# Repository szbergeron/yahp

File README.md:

WARN: Not ready for use yet

The boards are semi-final, but I need to finish part selection and push a new variant that allows varying sensor position.
Code is in Proof-of-Concept state, and has a lot of stuff hard-coded that should be pulled out into configs.

#Because getting an AvantGrand would just be way too easy

Inspired by [Greg Zweigle's DIY Hybrid Piano](https://github.com/gzweigle/DIY-Grand-Digital-Piano) and the [Cybrid Project](https://github.com/ekumanov/cybrid).

I don't come from a hardware/EE background, so a lot of that stuff was done by feel rather than through meticulous science. Instead, I tried to all of the "magic" through software. The sensors are probably not "ideal", but they are cheap and dumb simple. I didn't use trimmers or anything like that to calibrate, opting instead to gather raw measurements and then apply software correction. I also opted to use onboard ADCs instead of external ones or any kind of extra voltage reference. This absolutely introduces some inaccuracy in the lower bits of the raw measurements, but again--software magic :)

The flip side of using such a simple design from an EE perspective is that fabrication is _dumb simple_, even if technically more expensive when looking at the BOM. Each key uses a single sensor, and there is an MCU for every 16 keys, plus some basic power filtering all on a PCB. I'm spectacularly bad at soldering, so this has as little of it as I could get away with. This project is aimed at being an easy "kit" to get components for and assemble. Follow along if you'd like!

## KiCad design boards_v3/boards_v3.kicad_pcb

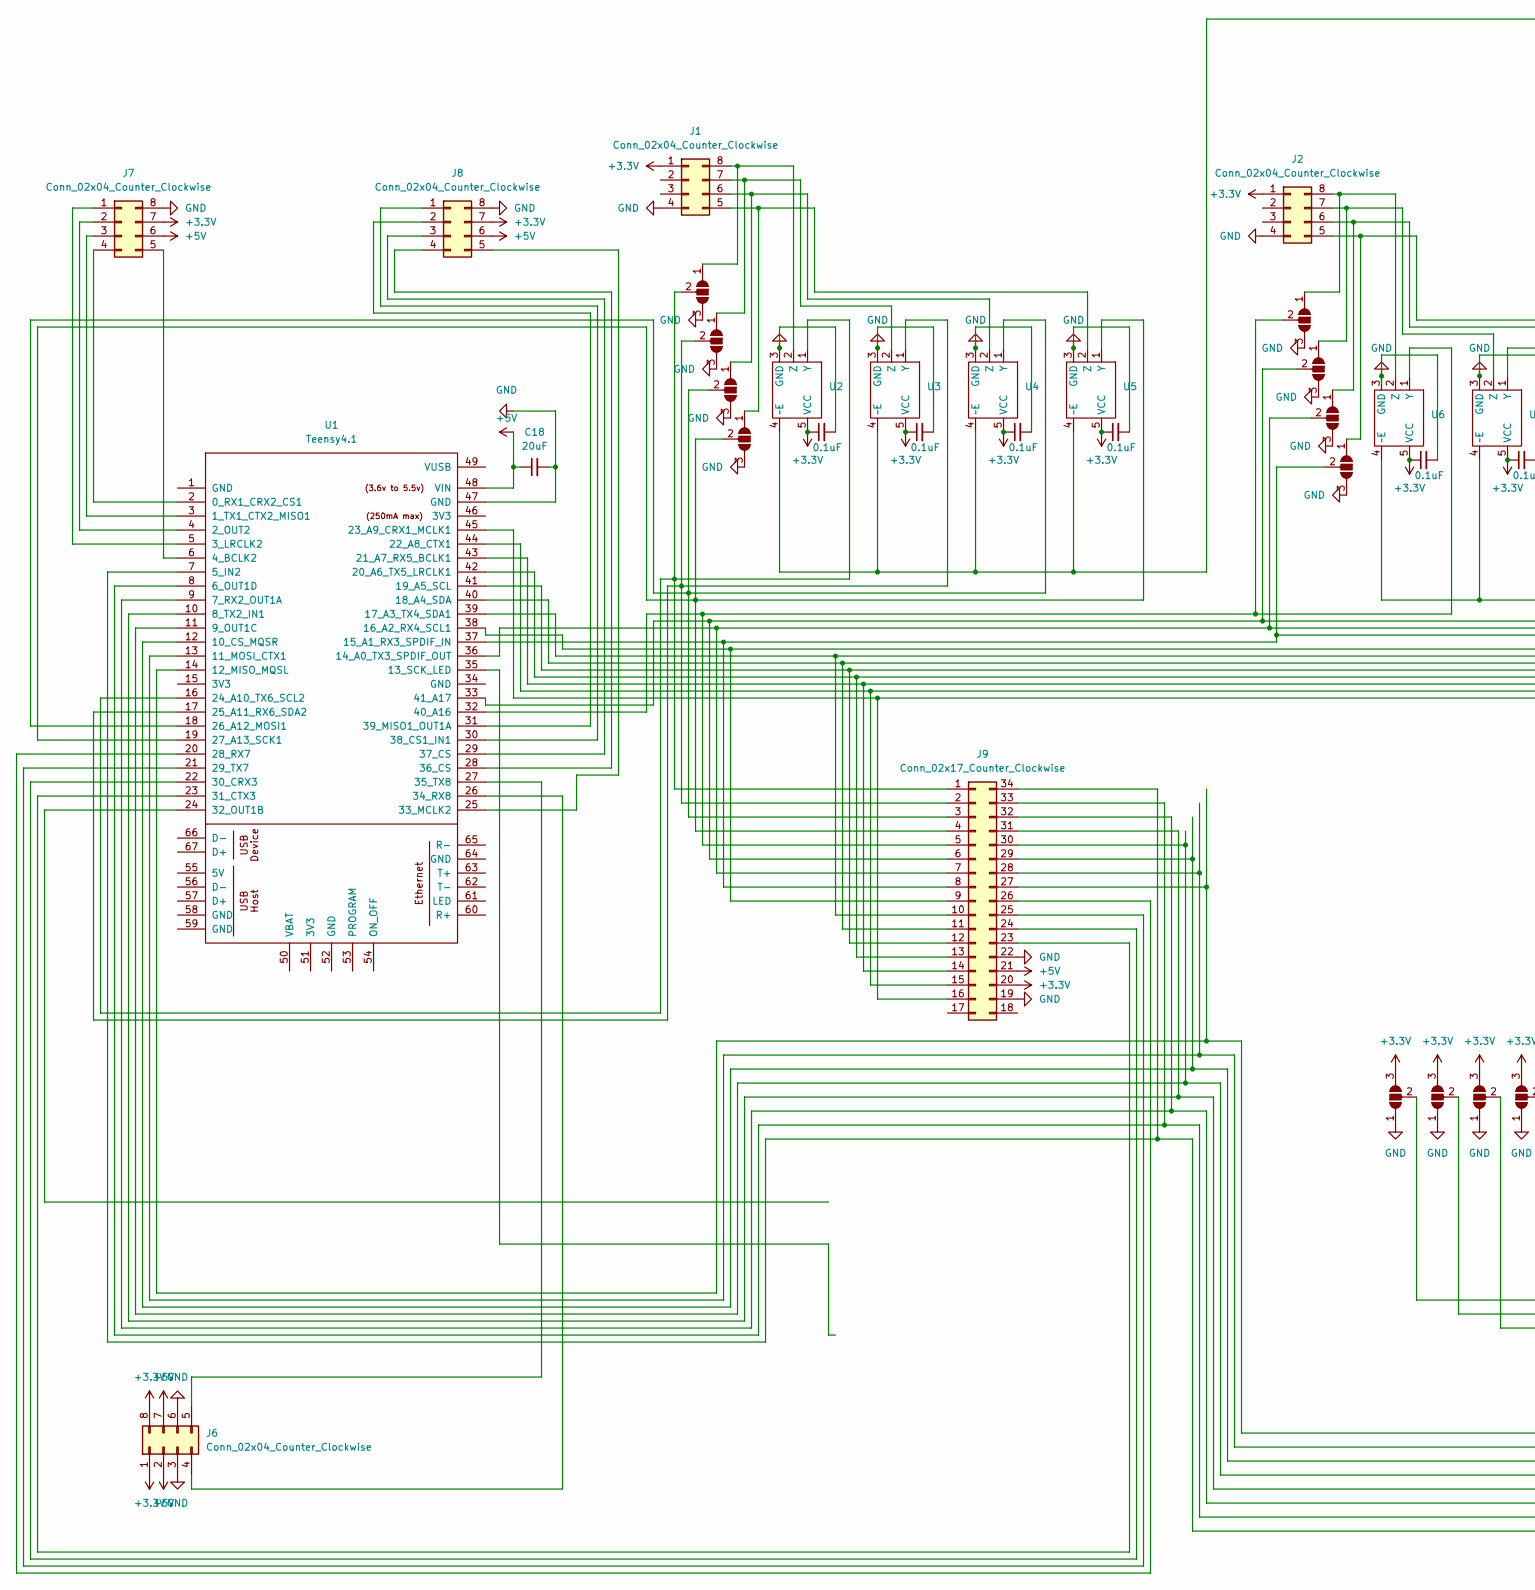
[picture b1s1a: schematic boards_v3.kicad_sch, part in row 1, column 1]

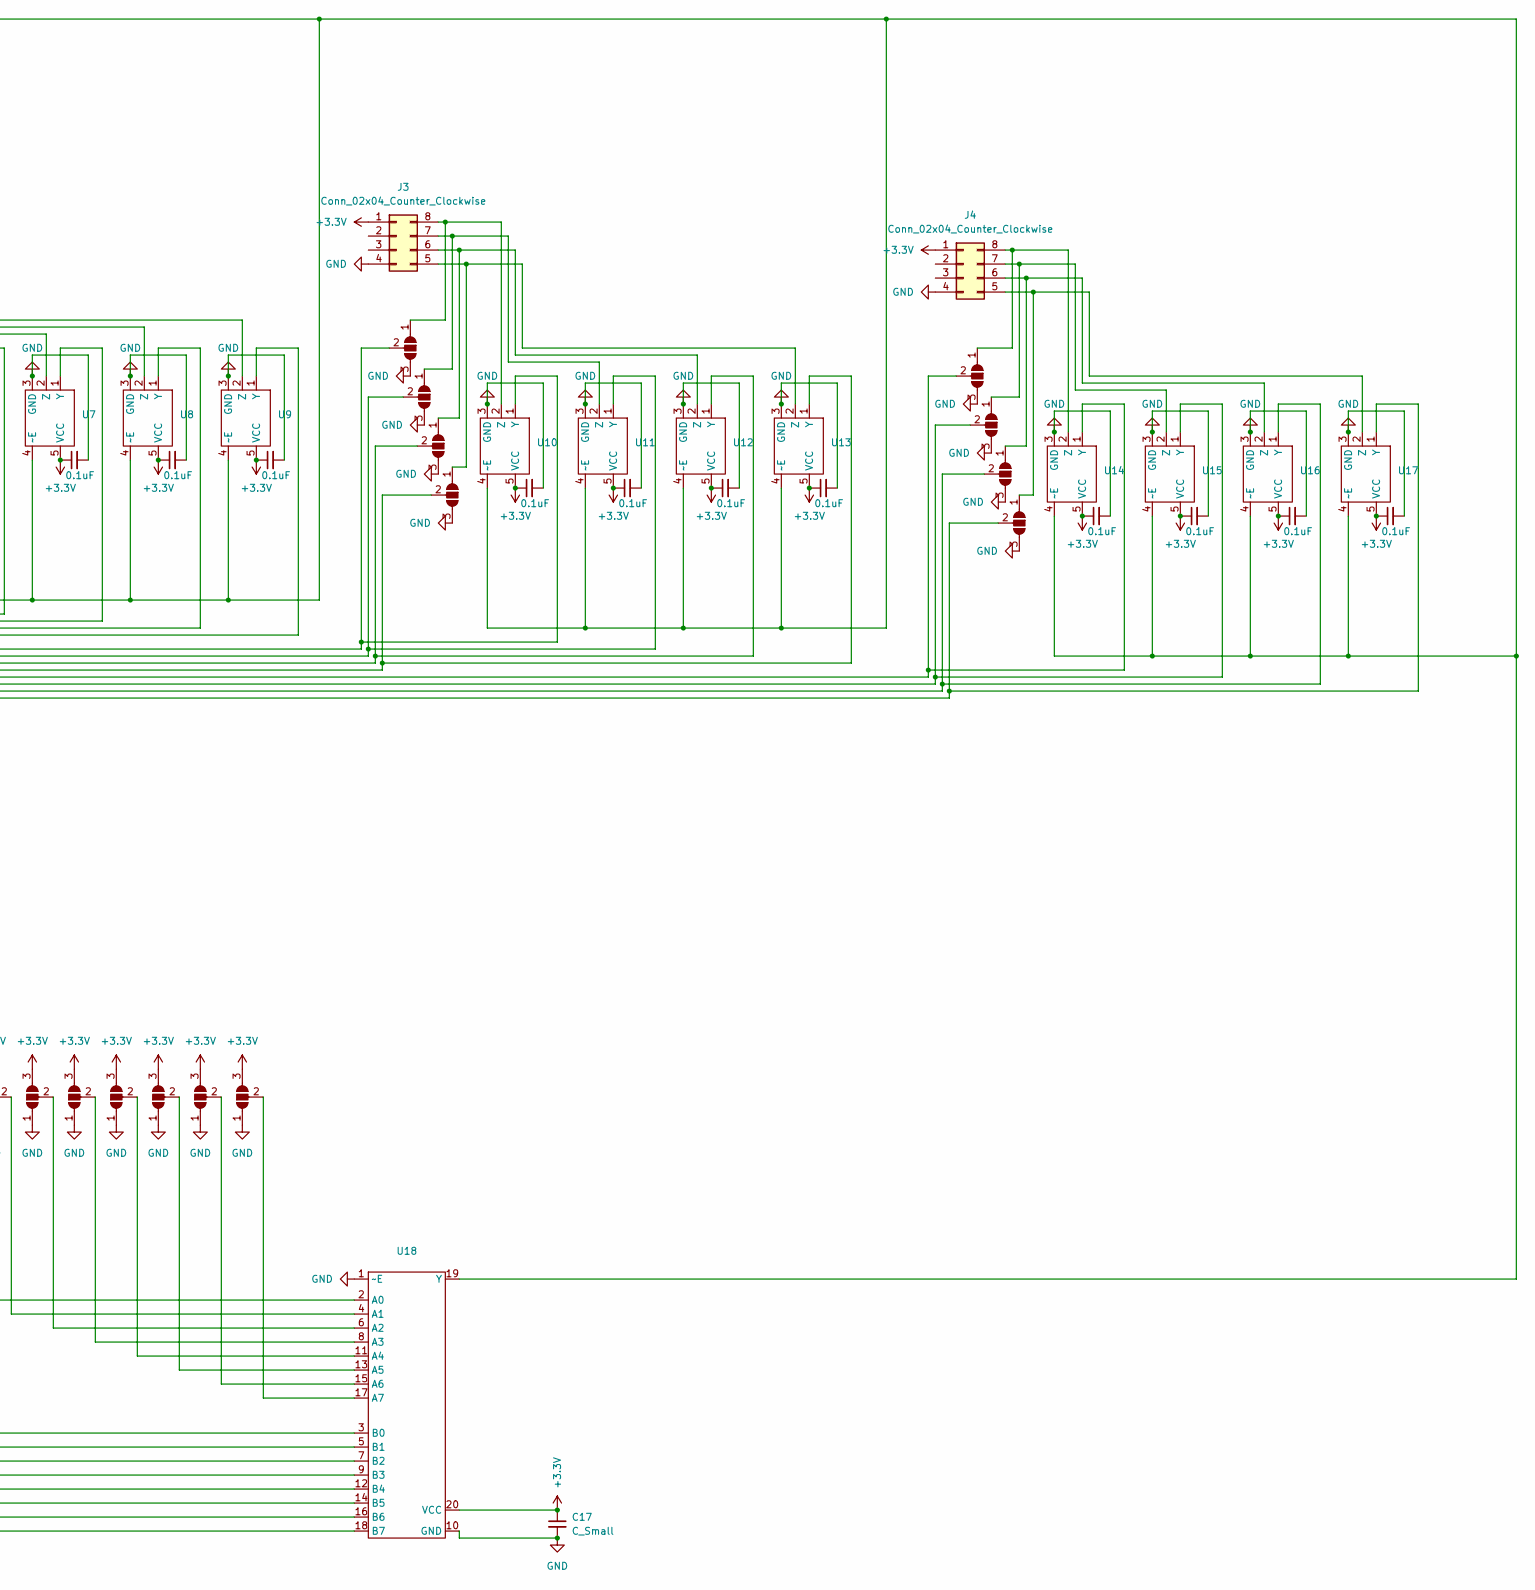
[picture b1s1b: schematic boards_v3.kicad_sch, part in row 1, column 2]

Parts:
C1, C2, C3, C4, C5, C6, C7, C8, C9, C10, C11, C12, C13, C14, C15, C16: 0.1uF; C_1206_3216Metric_Pad1.33x1.80mm_HandSolder
C17: C_Small; C_1206_3216Metric_Pad1.33x1.80mm_HandSolder
C18: 20uF; C_1812_4532Metric_Pad1.57x3.40mm_HandSolder
J1, J2, J3, J4, J6, J7, J8: Conn_02x04_Counter_Clockwise; Conn_02x04_2.54mm_pin
J9: Conn_02x17_Counter_Clockwise; Conn_02x17_2.54mm_pin
JP1, JP2, JP3, JP4, JP5, JP6, JP7, JP8, JP9, JP10, JP11, JP12, JP13, JP14, JP15, JP16, JP17, JP18, JP19, JP20, JP21, JP22, JP23, JP24: SolderJumper_3_Open; SolderJumper-3_P1.3mm_Open_RoundedPad1.0x1.5mm
U1: Teensy4.1; Teensy41
U2, U3, U4, U5, U6, U7, U8, U9, U10, U11, U12, U13, U14, U15, U16, U17: SC-74A-5_1.55x2.9mm_P0.95mm
U18: SOIC-20W_7.5x12.8mm_P1.27mm

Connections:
+3.3V: C1.1, C2.1, C3.1, C4.1, C5.1, C6.1, C7.1, C8.1, C9.1, C10.1, C11.1, C12.1, C13.1, C14.1, C15.1, C16.1, C17.1, J1.1, J2.1, J3.1, J4.1, J6.1, J6.8, J7.7, J8.7, J9.20, JP17.3 (B), JP18.3 (B), JP19.3 (B), JP20.3 (B), JP21.3 (B), JP22.3 (B), JP23.3 (B), JP24.3 (B), U2.5 (VCC), U3.5 (VCC), U4.5 (VCC), U5.5 (VCC), U6.5 (VCC), U7.5 (VCC), U8.5 (VCC), U9.5 (VCC), U10.5 (VCC), U11.5 (VCC), U12.5 (VCC), U13.5 (VCC), U14.5 (VCC), U15.5 (VCC), U16.5 (VCC), U17.5 (VCC), U18.20 (VCC)
+5V: C18.1, J6.2, J6.7, J7.6, J8.6, J9.21, U1.48 (VIN)
GND: C1.2, C2.2, C3.2, C4.2, C5.2, C6.2, C7.2, C8.2, C9.2, C10.2, C11.2, C12.2, C13.2, C14.2, C15.2, C16.2, C17.2, C18.2, J1.4, J2.4, J3.4, J4.4, J6.3, J6.6, J7.8, J8.8, J9.19, J9.22, JP1.3 (B), JP2.3 (B), JP3.3 (B), JP4.3 (B), JP5.3 (B), JP6.3 (B), JP7.3 (B), JP8.3 (B), JP9.3 (B), JP10.3 (B), JP11.3 (B), JP12.3 (B), JP13.3 (B), JP14.3 (B), JP15.3 (B), JP16.3 (B), JP17.1 (A), JP18.1 (A), JP19.1 (A), JP20.1 (A), JP21.1 (A), JP22.1 (A), JP23.1 (A), JP24.1 (A), U1.47 (GND), U2.3 (GND), U3.3 (GND), U4.3 (GND), U5.3 (GND), U6.3 (GND), U7.3 (GND), U8.3 (GND), U9.3 (GND), U10.3 (GND), U11.3 (GND), U12.3 (GND), U13.3 (GND), U14.3 (GND), U15.3 (GND), U16.3 (GND), U17.3 (GND), U18.1 (~E), U18.10 (GND)
unnamed: J1.5, JP4.1 (A), U5.2 (Z)
unnamed: J1.6, JP3.1 (A), U4.2 (Z)
unnamed: J1.7, JP2.1 (A), U3.2 (Z)
unnamed: J1.8, JP1.1 (A), U2.2 (Z)
unnamed: J2.5, JP8.1 (A), U9.2 (Z)
unnamed: J2.6, JP7.1 (A), U8.2 (Z)
unnamed: J2.7, JP6.1 (A), U7.2 (Z)
unnamed: J2.8, JP5.1 (A), U6.2 (Z)
unnamed: J3.5, JP12.1 (A), U13.2 (Z)
unnamed: J3.6, JP11.1 (A), U12.2 (Z)
unnamed: J3.7, JP10.1 (A), U11.2 (Z)
unnamed: J3.8, JP9.1 (A), U10.2 (Z)
unnamed: J4.5, JP16.1 (A), U17.2 (Z)
unnamed: J4.6, JP15.1 (A), U16.2 (Z)
unnamed: J4.7, JP14.1 (A), U15.2 (Z)
unnamed: J4.8, JP13.1 (A), U14.2 (Z)
unnamed: J6.4, U1.26 (34_RX8)
unnamed: J6.5, U1.27 (35_TX8)
unnamed: J7.1, U1.5 (3_LRCLK2)
unnamed: J7.2, U1.4 (2_OUT2)
unnamed: J7.3, U1.3 (1_TX1_CTX2_MISO1)
unnamed: J7.4, U1.2 (0_RX1_CRX2_CS1)
unnamed: J7.5, U1.6 (4_BCLK2)
unnamed: J8.1, U1.30 (38_CS1_IN1)
unnamed: J8.2, U1.31 (39_MISO1_OUT1A)
unnamed: J8.3, U1.29 (37_CS)
unnamed: J8.4, U1.28 (36_CS)
unnamed: J8.5, U1.25 (33_MCLK2)
unnamed: J9.1, JP1.2 (C), U1.16 (24_A10_TX6_SCL2), U2.1 (Y)
unnamed: J9.2, JP2.2 (C), U1.17 (25_A11_RX6_SDA2), U3.1 (Y)
unnamed: J9.3, JP3.2 (C), U1.18 (26_A12_MOSI1), U4.1 (Y)
unnamed: J9.4, JP4.2 (C), U1.19 (27_A13_SCK1), U5.1 (Y)
unnamed: J9.5, JP5.2 (C), U1.32 (40_A16), U6.1 (Y)
unnamed: J9.6, JP6.2 (C), U1.33 (41_A17), U7.1 (Y)
unnamed: J9.7, JP7.2 (C), U1.36 (14_A0_TX3_SPDIF_OUT), U8.1 (Y)
unnamed: J9.8, JP8.2 (C), U1.37 (15_A1_RX3_SPDIF_IN), U9.1 (Y)
unnamed: J9.9, JP9.2 (C), U1.38 (16_A2_RX4_SCL1), U10.1 (Y)
unnamed: J9.10, JP10.2 (C), U1.39 (17_A3_TX4_SDA1), U11.1 (Y)
unnamed: J9.11, JP11.2 (C), U1.40 (18_A4_SDA), U12.1 (Y)
unnamed: J9.12, JP12.2 (C), U1.41 (19_A5_SCL), U13.1 (Y)
unnamed: J9.13, JP13.2 (C), U1.42 (20_A6_TX5_LRCLK1), U14.1 (Y)
unnamed: J9.14, JP14.2 (C), U1.43 (21_A7_RX5_BCLK1), U15.1 (Y)
unnamed: J9.15, JP15.2 (C), U1.44 (22_A8_CTX1), U16.1 (Y)
unnamed: J9.16, JP16.2 (C), U1.45 (23_A9_CRX1_MCLK1), U17.1 (Y)
unnamed: J9.23, U1.23 (31_CTX3)
unnamed: J9.24, U1.22 (30_CRX3)
unnamed: J9.25, U1.21 (29_TX7)
unnamed: J9.26, U1.20 (28_RX7)
unnamed: J9.27, U1.14 (12_MISO_MQSL), U18.3 (B0)
unnamed: J9.28, U1.13 (11_MOSI_CTX1), U18.5 (B1)
unnamed: J9.29, U1.12 (10_CS_MQSR), U18.7 (B2)
unnamed: J9.30, U1.11 (9_OUT1C), U18.9 (B3)
unnamed: J9.31, U1.10 (8_TX2_IN1), U18.12 (B4)
unnamed: J9.32, U1.9 (7_RX2_OUT1A), U18.14 (B5)
unnamed: J9.33, U1.8 (6_OUT1D), U18.16 (B6)
unnamed: J9.34, U1.7 (5_IN2), U18.18 (B7)
unnamed: JP17.2 (C), U18.2 (A0)
unnamed: JP18.2 (C), U18.4 (A1)
unnamed: JP19.2 (C), U18.6 (A2)
unnamed: JP20.2 (C), U18.8 (A3)
unnamed: JP21.2 (C), U18.11 (A4)
unnamed: JP22.2 (C), U18.13 (A5)
unnamed: JP23.2 (C), U18.15 (A6)
unnamed: JP24.2 (C), U18.17 (A7)
unnamed: U2.4 (~E), U3.4 (~E), U4.4 (~E), U5.4 (~E), U6.4 (~E), U7.4 (~E), U8.4 (~E), U9.4 (~E), U10.4 (~E), U11.4 (~E), U12.4 (~E), U13.4 (~E), U14.4 (~E), U15.4 (~E), U16.4 (~E), U17.4 (~E), U18.19 (Y)

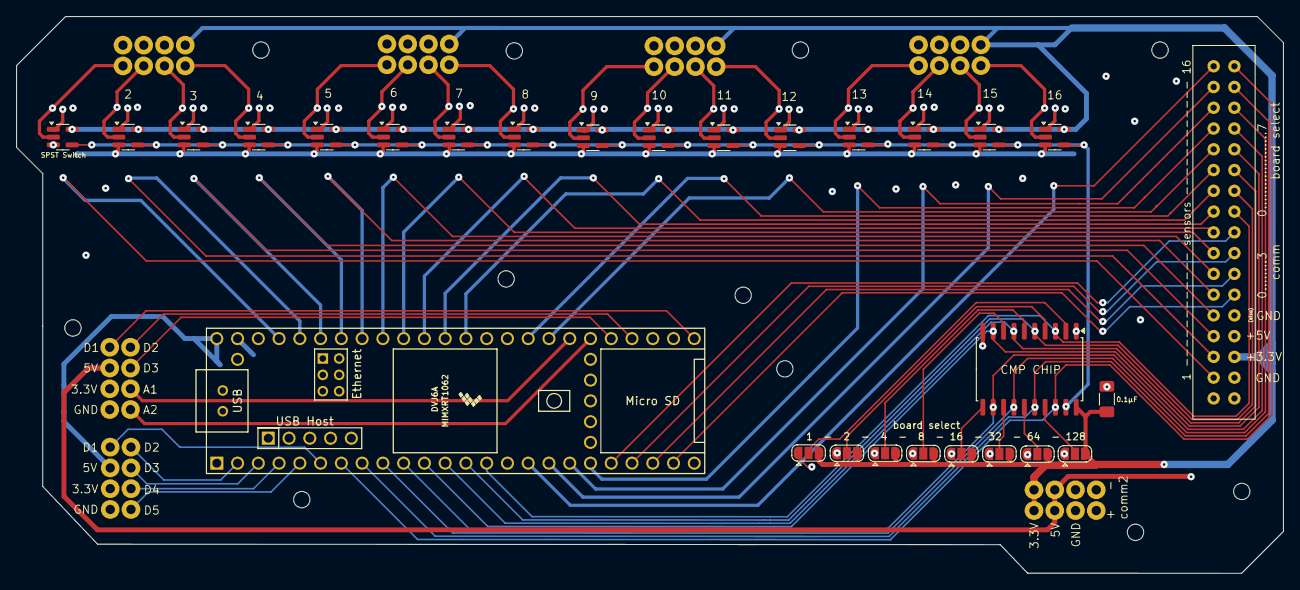
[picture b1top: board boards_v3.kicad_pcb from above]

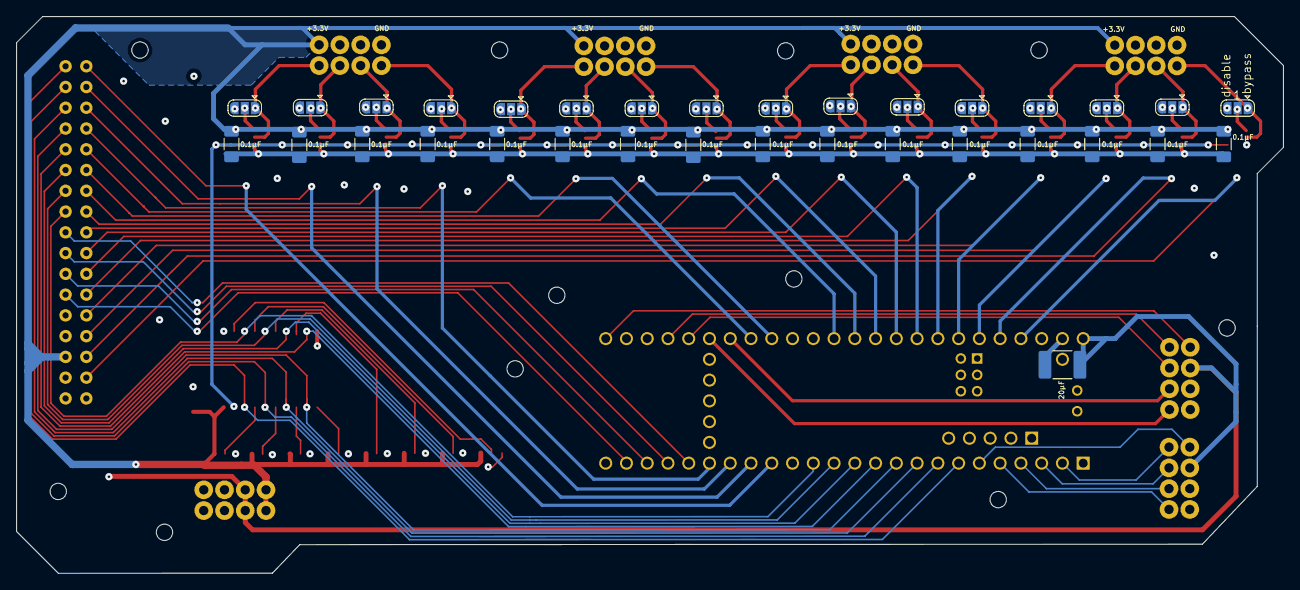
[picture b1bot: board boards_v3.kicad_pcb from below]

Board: 4 copper layers, 155.0 x 68.1 mm, 68 parts (33 on the bottom side), 68 nets.

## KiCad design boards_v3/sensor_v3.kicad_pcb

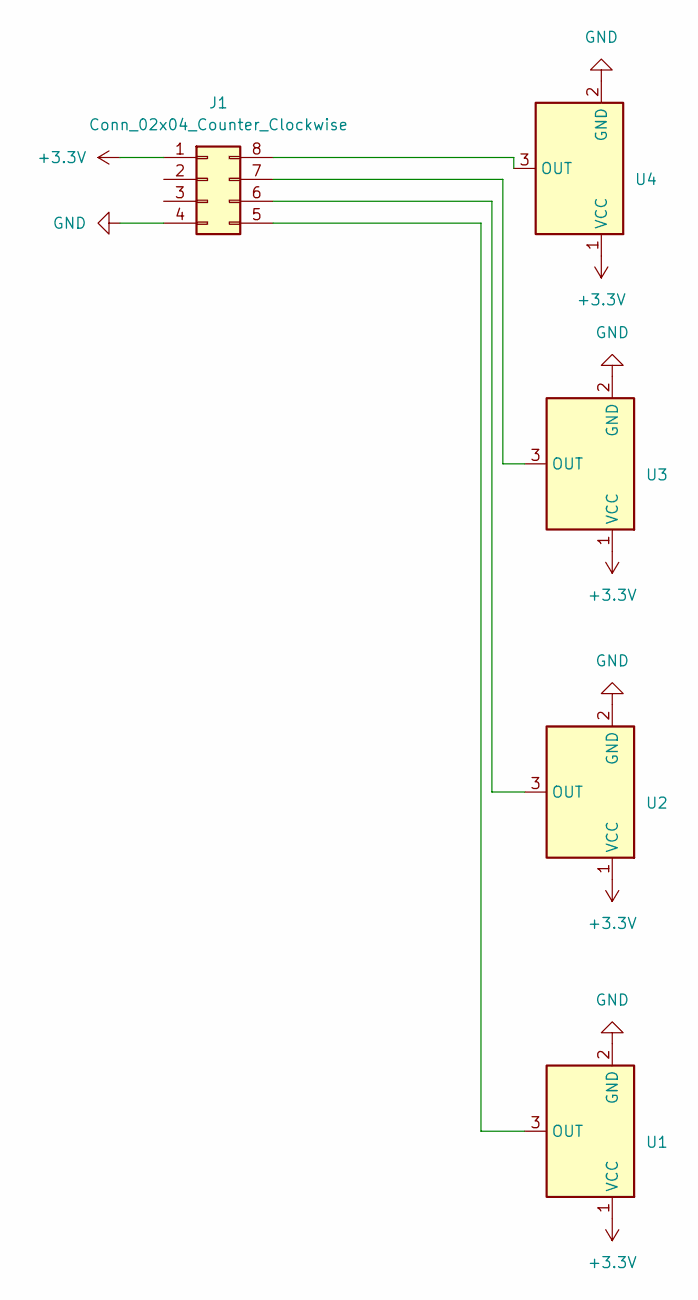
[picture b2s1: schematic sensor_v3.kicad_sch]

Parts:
J1: Conn_02x04_Counter_Clockwise; Conn_02x04_2.54mm_pin
U1, U2, U3, U4: DRV5055A1xLPGxQ1; TO-92_Inline_Wide

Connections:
+3.3V: J1.1, U1.1 (VCC), U2.1 (VCC), U3.1 (VCC), U4.1 (VCC)
GND: J1.4, U1.2 (GND), U2.2 (GND), U3.2 (GND), U4.2 (GND)
unnamed: J1.5, U1.3 (OUT)
unnamed: J1.6, U2.3 (OUT)
unnamed: J1.7, U3.3 (OUT)
unnamed: J1.8, U4.3 (OUT)

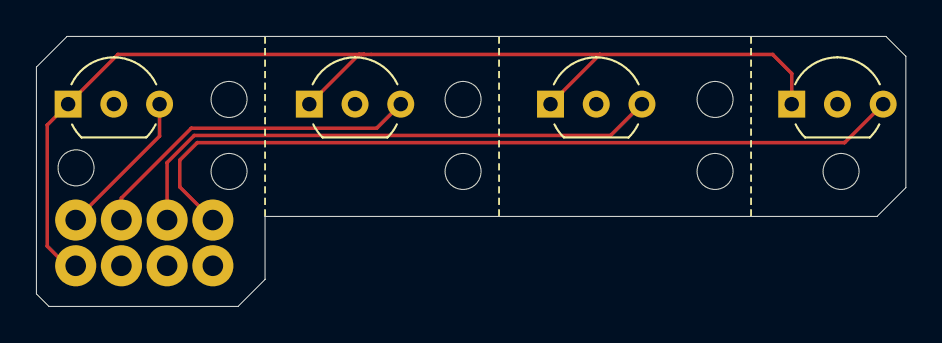
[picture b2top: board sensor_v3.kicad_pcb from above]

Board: 2 copper layers, 48.3 x 15.0 mm, 5 parts (0 on the bottom side), 6 nets.
